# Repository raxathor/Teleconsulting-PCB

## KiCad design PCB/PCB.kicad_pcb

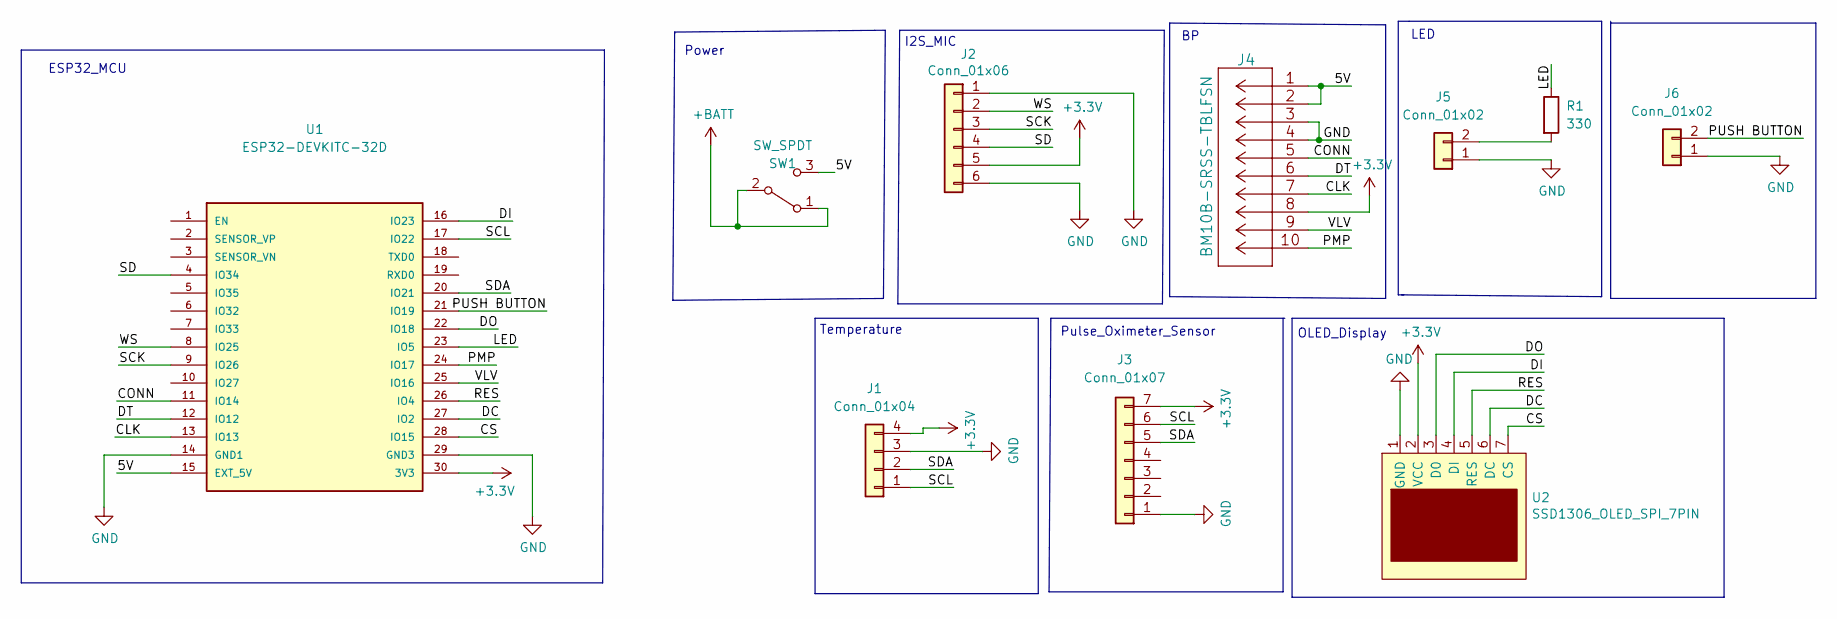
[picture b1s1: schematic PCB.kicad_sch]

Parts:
J1: Conn_01x04; PinHeader_1x04_P2.54mm_Vertical
J2: Conn_01x06; PinHeader_1x06_P2.54mm_Vertical
J3: Conn_01x07; PinHeader_1x07_P2.54mm_Vertical
J4: BM10B-SRSS-TBLFSN; SM10B-SRSS-TB; Manufacturer_Part_Number BM10B-SRSS-TBLFSN
J5, J6: Conn_01x02; PinHeader_1x02_P2.54mm_Vertical
R1: 330; R_0805_2012Metric_Pad1.20x1.40mm_HandSolder
SW1: SW_SPDT; PinHeader_1x02_P2.54mm_Vertical
U1: ESP32-DEVKITC-32D; PARTREV 4
U2: SSD1306_OLED_SPI_7PIN; PinHeader_1x07_P2.54mm_Vertical

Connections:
+3V3: J1.4, J2.5, J3.7, J4.8, U1.30 (3V3), U2.2 (VCC)
+BATT: SW1.1 (A), SW1.2 (B)
/5V: J4.1, J4.2, SW1.3 (C), U1.15 (EXT_5V)
/CLK: J4.7, U1.13 (IO13)
/CONN: J4.5, U1.11 (IO14)
/CS: U1.28 (IO15), U2.7 (CS)
/DC: U1.27 (IO2), U2.6 (DC)
/DI: U1.16 (IO23), U2.4 (DI)
/DO: U1.22 (IO18), U2.3 (D0)
/DT: J4.6, U1.12 (IO12)
/LED: R1.1, U1.23 (IO5)
/PMP: J4.10, U1.24 (IO17)
/PUSH BUTTON: J6.2, U1.21 (IO19)
/RES: U1.26 (IO4), U2.5 (RES)
/SCK: J2.3, U1.9 (IO26)
/SCL: J1.1, J3.6, U1.17 (IO22)
/SD: J2.4, U1.4 (IO34)
/SDA: J1.2, J3.5, U1.20 (IO21)
/VLV: J4.9, U1.25 (IO16)
/WS: J2.2, U1.8 (IO25)
GND: J1.3, J2.1, J2.6, J3.1, J4.3, J4.4, J5.1, J6.1, U1.14 (GND1), U1.29 (GND3), U2.1 (GND)
unnamed: J5.2, R1.2

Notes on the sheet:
LED
Pulse_Oximeter_Sensor
Power
OLED_Display
Temperature
ESP32_MCU
I2S_MIC

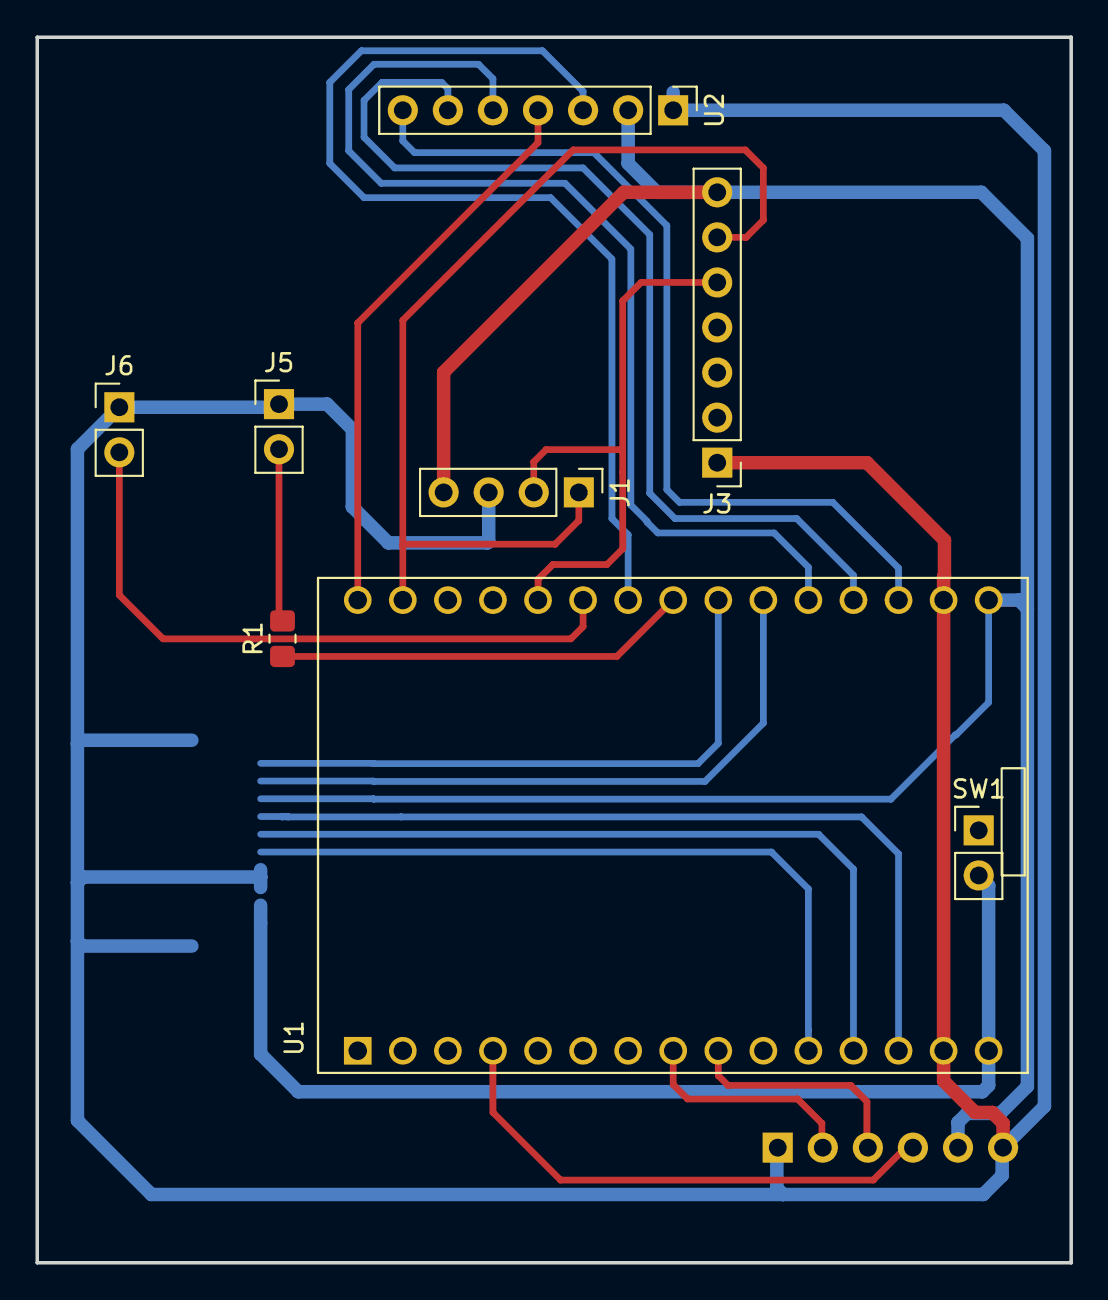
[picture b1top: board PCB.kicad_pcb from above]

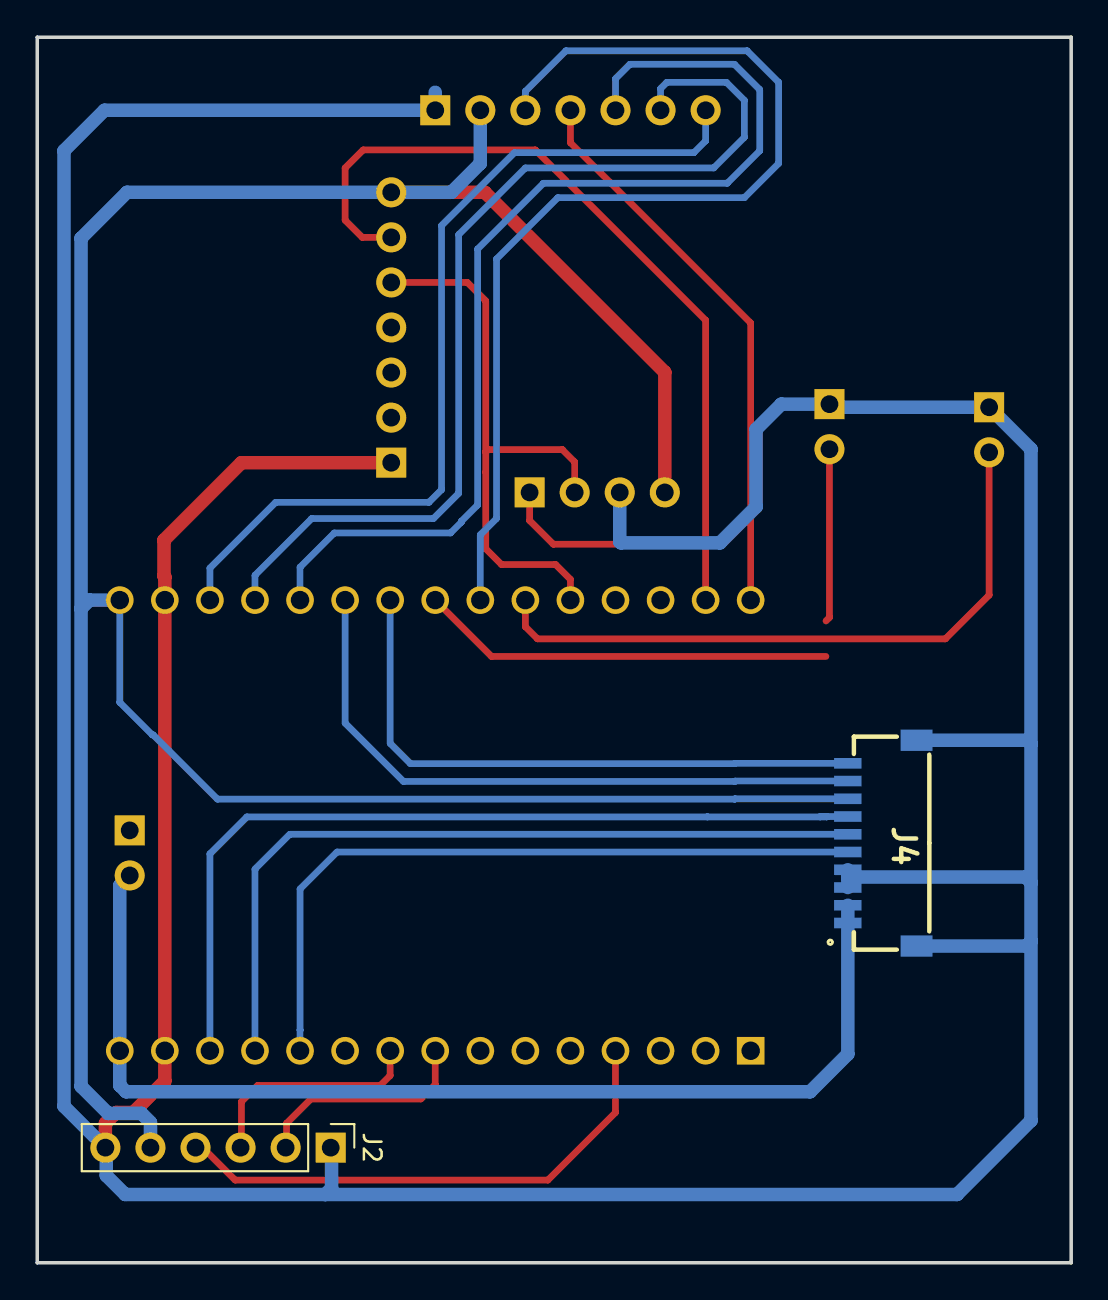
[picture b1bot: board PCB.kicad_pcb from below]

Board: 2 copper layers, 58.3 x 69.1 mm, 10 parts (2 on the bottom side), 21 nets.
